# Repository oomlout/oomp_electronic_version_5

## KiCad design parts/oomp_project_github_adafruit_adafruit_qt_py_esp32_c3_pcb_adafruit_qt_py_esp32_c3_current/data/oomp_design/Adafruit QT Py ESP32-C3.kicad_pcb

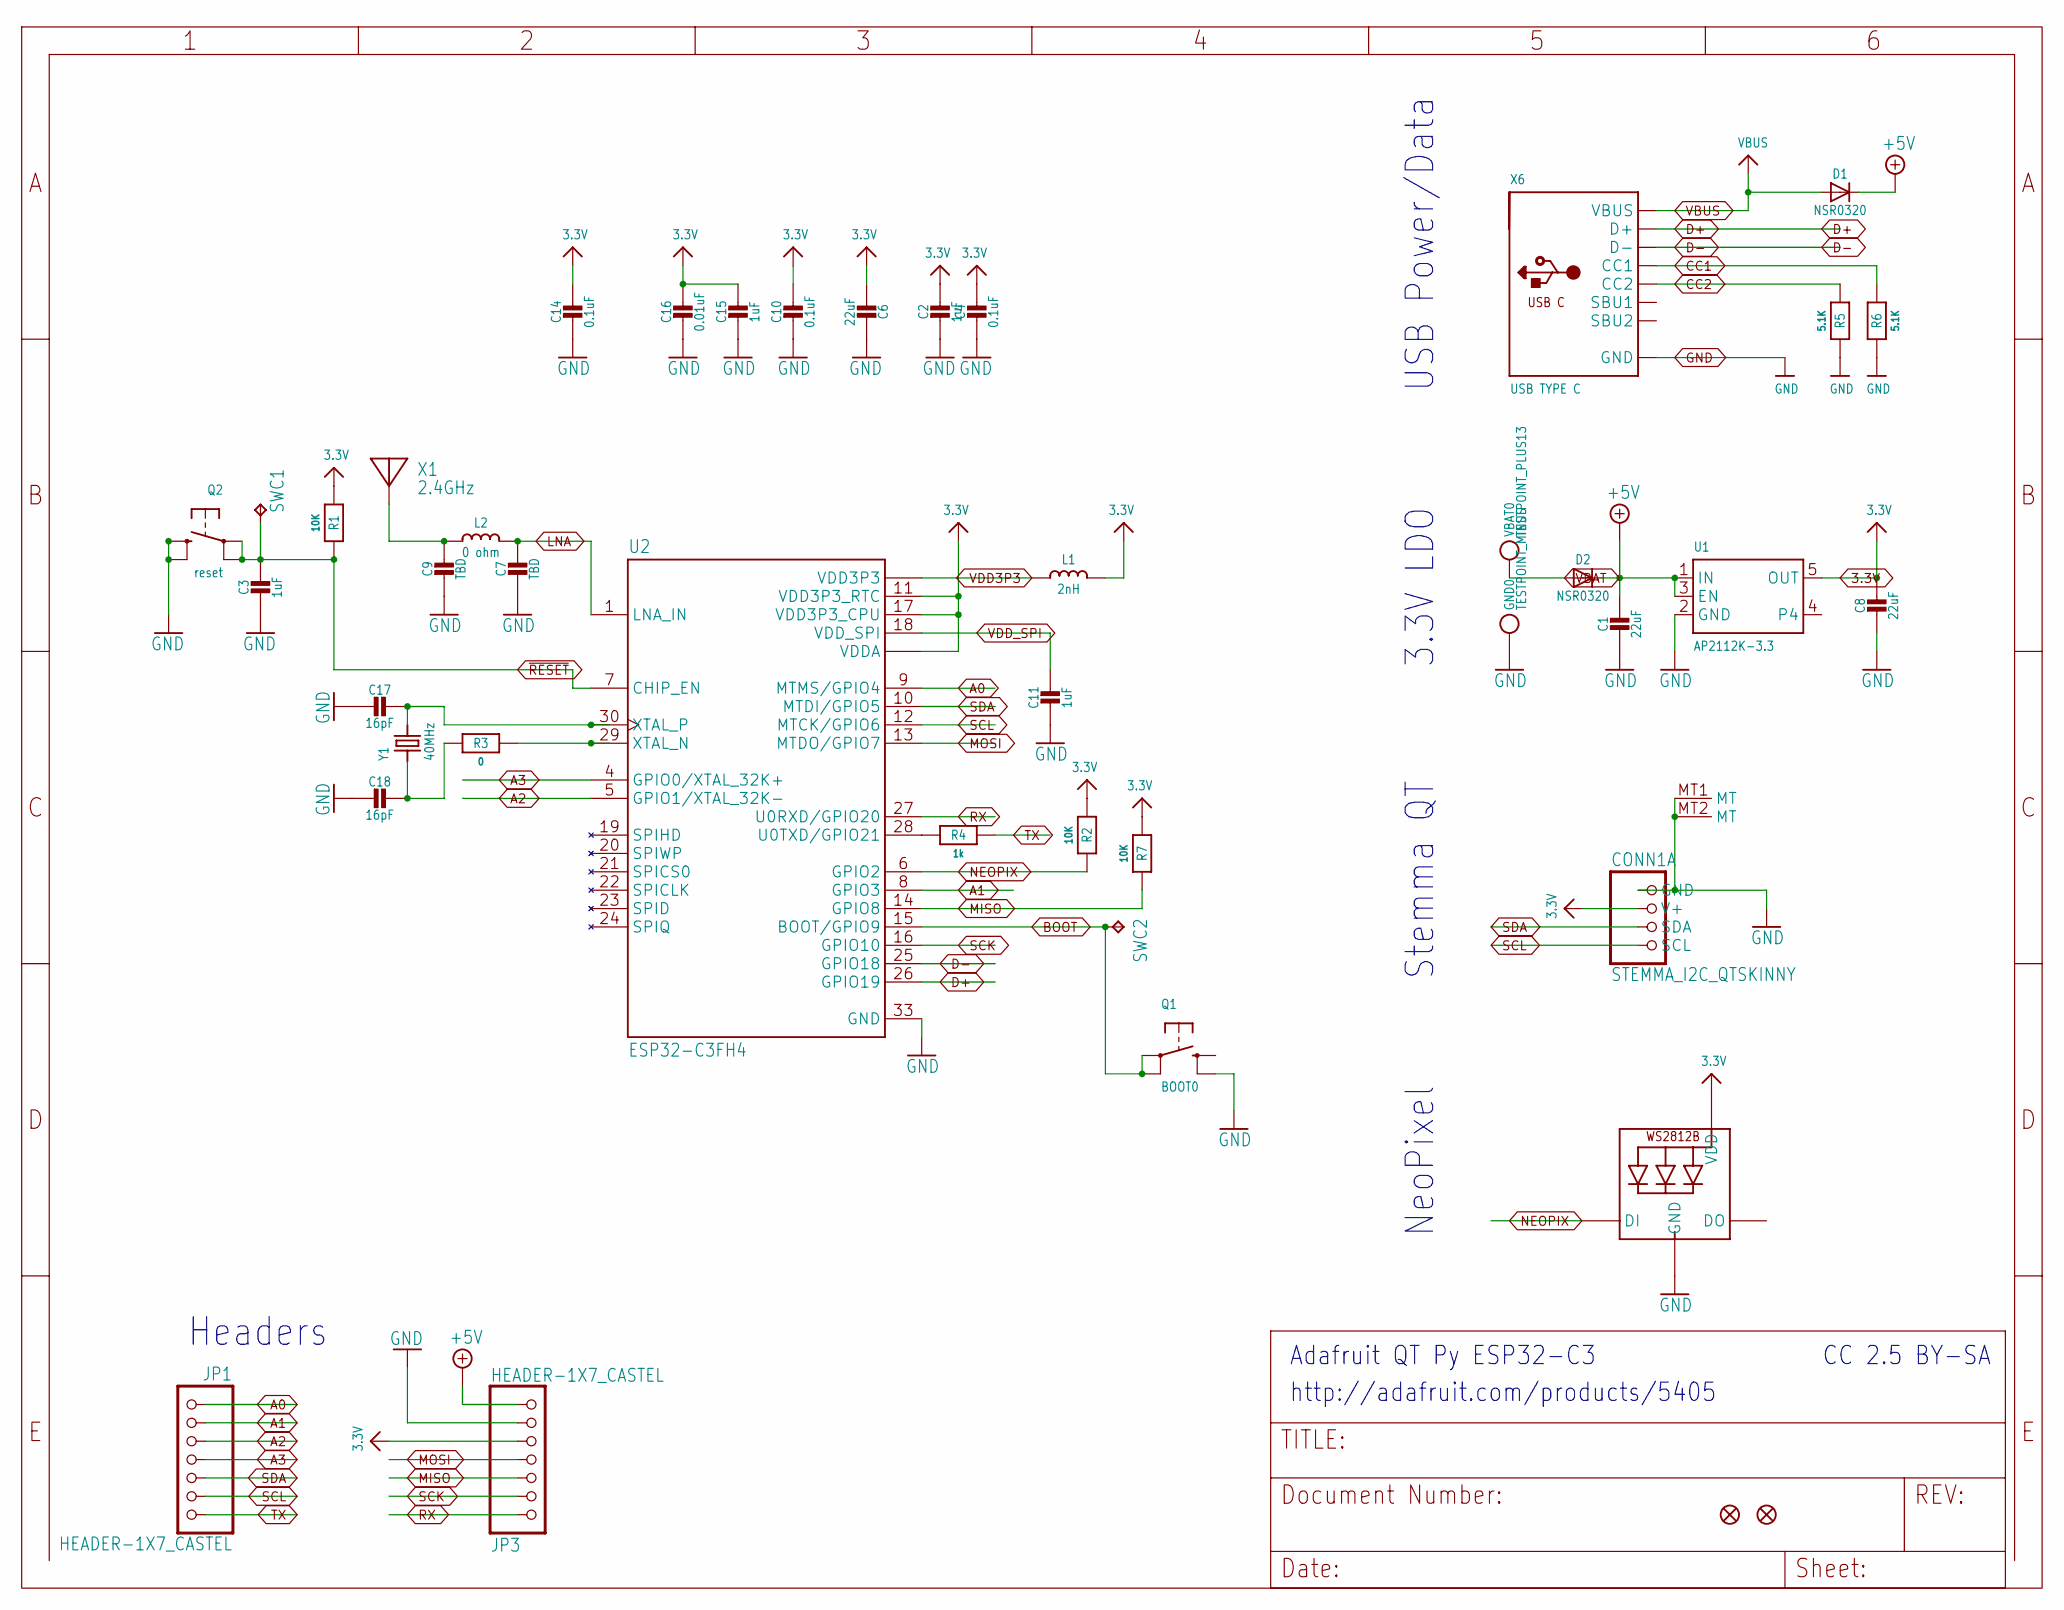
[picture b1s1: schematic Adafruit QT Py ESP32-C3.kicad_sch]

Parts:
C1, C6, C8: 22uF; 0805-NO
C2, C3, C11, C15: 1uF; _0402NO
C4, C10, C14: 0.1uF; _0402NO
C7, C9: TBD; _0402NO
C16: 0.01uF; _0402NO
C17, C18: 16pF; _0402NO
CONN1: STEMMA_I2C_QTSKINNY; JST_SH4_SKINNY
D1, D2: NSR0320; SOD-323_MINI
GND0: TESTPOINT_MINUS; TESTPOINT_MINUS_1X3MM
JP1, JP3: HEADER-1X7_CASTEL; 1X07_CASTEL
L1: 2nH; _0402
L2: 0 ohm; _0402
LED1: WS2812B_SK6805_1515; SK6805_1515
Q1: BOOT0; BTN_KMR2_4.6X2.8
Q2: reset; BTN_KMR2_SLIM
R1, R2: 10K; _0402NO
R3: 0; _0402NO
R4: 1k; _0402NO
R5, R6: 5.1K; _0402NO
R7: 10K; _0603MP_TWO6MIL
SWC1, SWC2: TPB1,27; B1,27
U1: AP2112K-3.3; SOT23-5
U2: ESP32-C3FH4; QFN32_5MM; DIGI-KEY_PART_NUMBER 1904-ESP32-C3FH4CT-ND
U$6, U$8: FIDUCIAL_1MM
VBAT0: TESTPOINT_PLUS13; TESTPOINT_PLUS_1X3MM
X1: 2.4GHz; ANT_2450AT18B100
X6: USB TYPE C; USB_C_CUSB31-CFM2AX-01-X
Y1: 40MHz; CRYSTAL_2X1.6

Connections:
3.3V: C2.1, C4.1, C6.1, C8.1, C10.1, C14.1, C15.1, C16.1, CONN1.2 (V+), JP3.5, JP3.5C (5), L1.1, LED1.2 (VDD), R1.1, R2.1, R7.1, U1.5 (OUT), U2.11 (VDD3P3_RTC), U2.17 (VDD3P3_CPU), U2.31 (VDDA), U2.32 (VDDA)
+5V: C1.1, D1.C, D2.C, JP3.7, JP3.7C (7), U1.1 (IN), U1.3 (EN)
A0: JP1.1, JP1.1C (1), U2.9 (MTMS/GPIO4)
A1: JP1.2, JP1.2C (2), U2.8 (GPIO3)
A2: JP1.3, JP1.3C (3), U2.5 (GPIO1/XTAL_32K-)
A3: JP1.4, JP1.4C (4), U2.4 (GPIO0/XTAL_32K+)
BOOT: Q1.A, Q1.A' (P1), SWC2.TP, U2.15 (BOOT/GPIO9)
CC1: R6.2, X6.A5 (CC1)
CC2: R5.2, X6.B5 (CC2)
D+: U2.26 (GPIO19), X6.A6 (D+), X6.B6 (D+)
D-: U2.25 (GPIO18), X6.A7 (D-), X6.B7 (D-)
GND: C1.2, C2.2, C3.2, C4.2, C6.2, C7.2, C8.2, C9.2, C10.2, C11.2, C14.2, C15.2, C16.2, C17.2, C18.2, CONN1.1 (GND), CONN1.MT1 (MT), CONN1.MT2 (MT), GND0.P$1, JP3.6, JP3.6C (6), LED1.4 (GND), Q1.B' (S1), Q2.B (S), Q2.B' (S1), R5.1, R6.1, U1.2 (GND), U2.33 (GND), X6.A1B12 (GND), X6.B1A12 (GND)
LNA: C7.1, L2.2, U2.1 (LNA_IN)
MISO: JP3.3, JP3.3C (3), R7.2, U2.14 (GPIO8)
MOSI: JP3.4, JP3.4C (4), U2.13 (MTDO/GPIO7)
unnamed: R4.1, U2.28 (U0TXD/GPIO21)
unnamed: C9.1, L2.1, X1.FP
unnamed: R3.2, U2.29 (XTAL_N)
unnamed: C17.1, U2.30 (XTAL_P), Y1.3 (2)
unnamed: C18.1, R3.1, Y1.1
NEOPIX: LED1.1 (DI), R2.2, U2.6 (GPIO2)
RX: JP3.1, JP3.1C (1), U2.27 (U0RXD/GPIO20)
SCK: JP3.2, JP3.2C (2), U2.16 (GPIO10)
SCL: CONN1.4 (SCL), JP1.6, JP1.6C (6), U2.12 (MTCK/GPIO6)
SDA: CONN1.3 (SDA), JP1.5, JP1.5C (5), U2.10 (MTDI/GPIO5)
TX: JP1.7, JP1.7C (7), R4.2
VBAT: D2.A, VBAT0.P$1
VBUS: D1.A, X6.A4B9 (VBUS), X6.B4A9 (VBUS)
VDD3P3: L1.2, U2.2 (VDD3P3), U2.3 (VDD3P3)
VDD_SPI: C11.1, U2.18 (VDD_SPI)
~RESET: C3.1, Q2.A, Q2.A' (P1), R1.2, SWC1.TP, U2.7 (CHIP_EN)

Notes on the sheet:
Adafruit QT Py ESP32-C3
http://adafruit.com/products/5405
CC 2.5 BY-SA
Stemma QT
USB Power/Data
Headers
NeoPixel
3.3V LDO

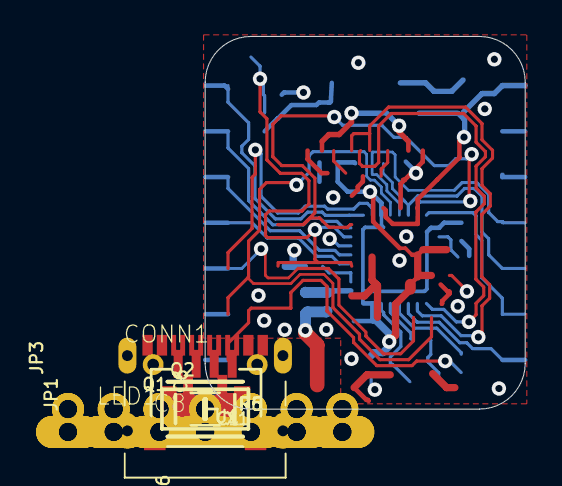
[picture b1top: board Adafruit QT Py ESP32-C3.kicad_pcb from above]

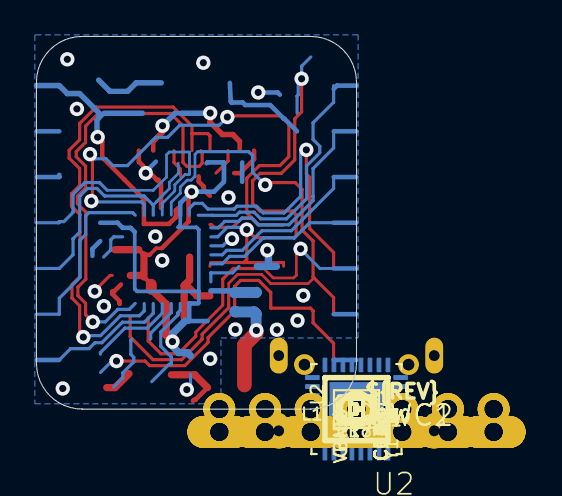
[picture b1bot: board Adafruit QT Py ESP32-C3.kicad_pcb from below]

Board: 4 copper layers, 17.8 x 20.7 mm, 46 parts (29 on the bottom side), 31 nets.

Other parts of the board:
U$3: QTPYC3_TOP
U$12: PCBFEAT-REV-040
U$18: QTPYC3_BOT

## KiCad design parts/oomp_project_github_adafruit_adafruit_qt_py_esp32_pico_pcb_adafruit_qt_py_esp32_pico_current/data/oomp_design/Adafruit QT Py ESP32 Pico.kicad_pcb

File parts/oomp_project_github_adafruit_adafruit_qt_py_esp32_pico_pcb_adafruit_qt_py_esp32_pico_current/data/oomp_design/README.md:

# OOMP KiCad design copy

Open `Adafruit QT Py ESP32 Pico.kicad_pro` (or the `.kicad_pcb` / `.kicad_sch`) in KiCad. Local OOMP libraries are under `libraries/`. Original inputs are preserved in [../original/](../original/).

Only verified unchanged installed KiCad defaults were renamed. Modified, custom, unmatched and unavailable items remain unchanged. Soldering variants are never swapped during conversion. Existing pad coordinates, nets and UUIDs are preserved.

See [conversion_report.yaml](conversion_report.yaml) for every conversion and skip. Copy this directory before editing; regeneration refuses to overwrite edited design files.

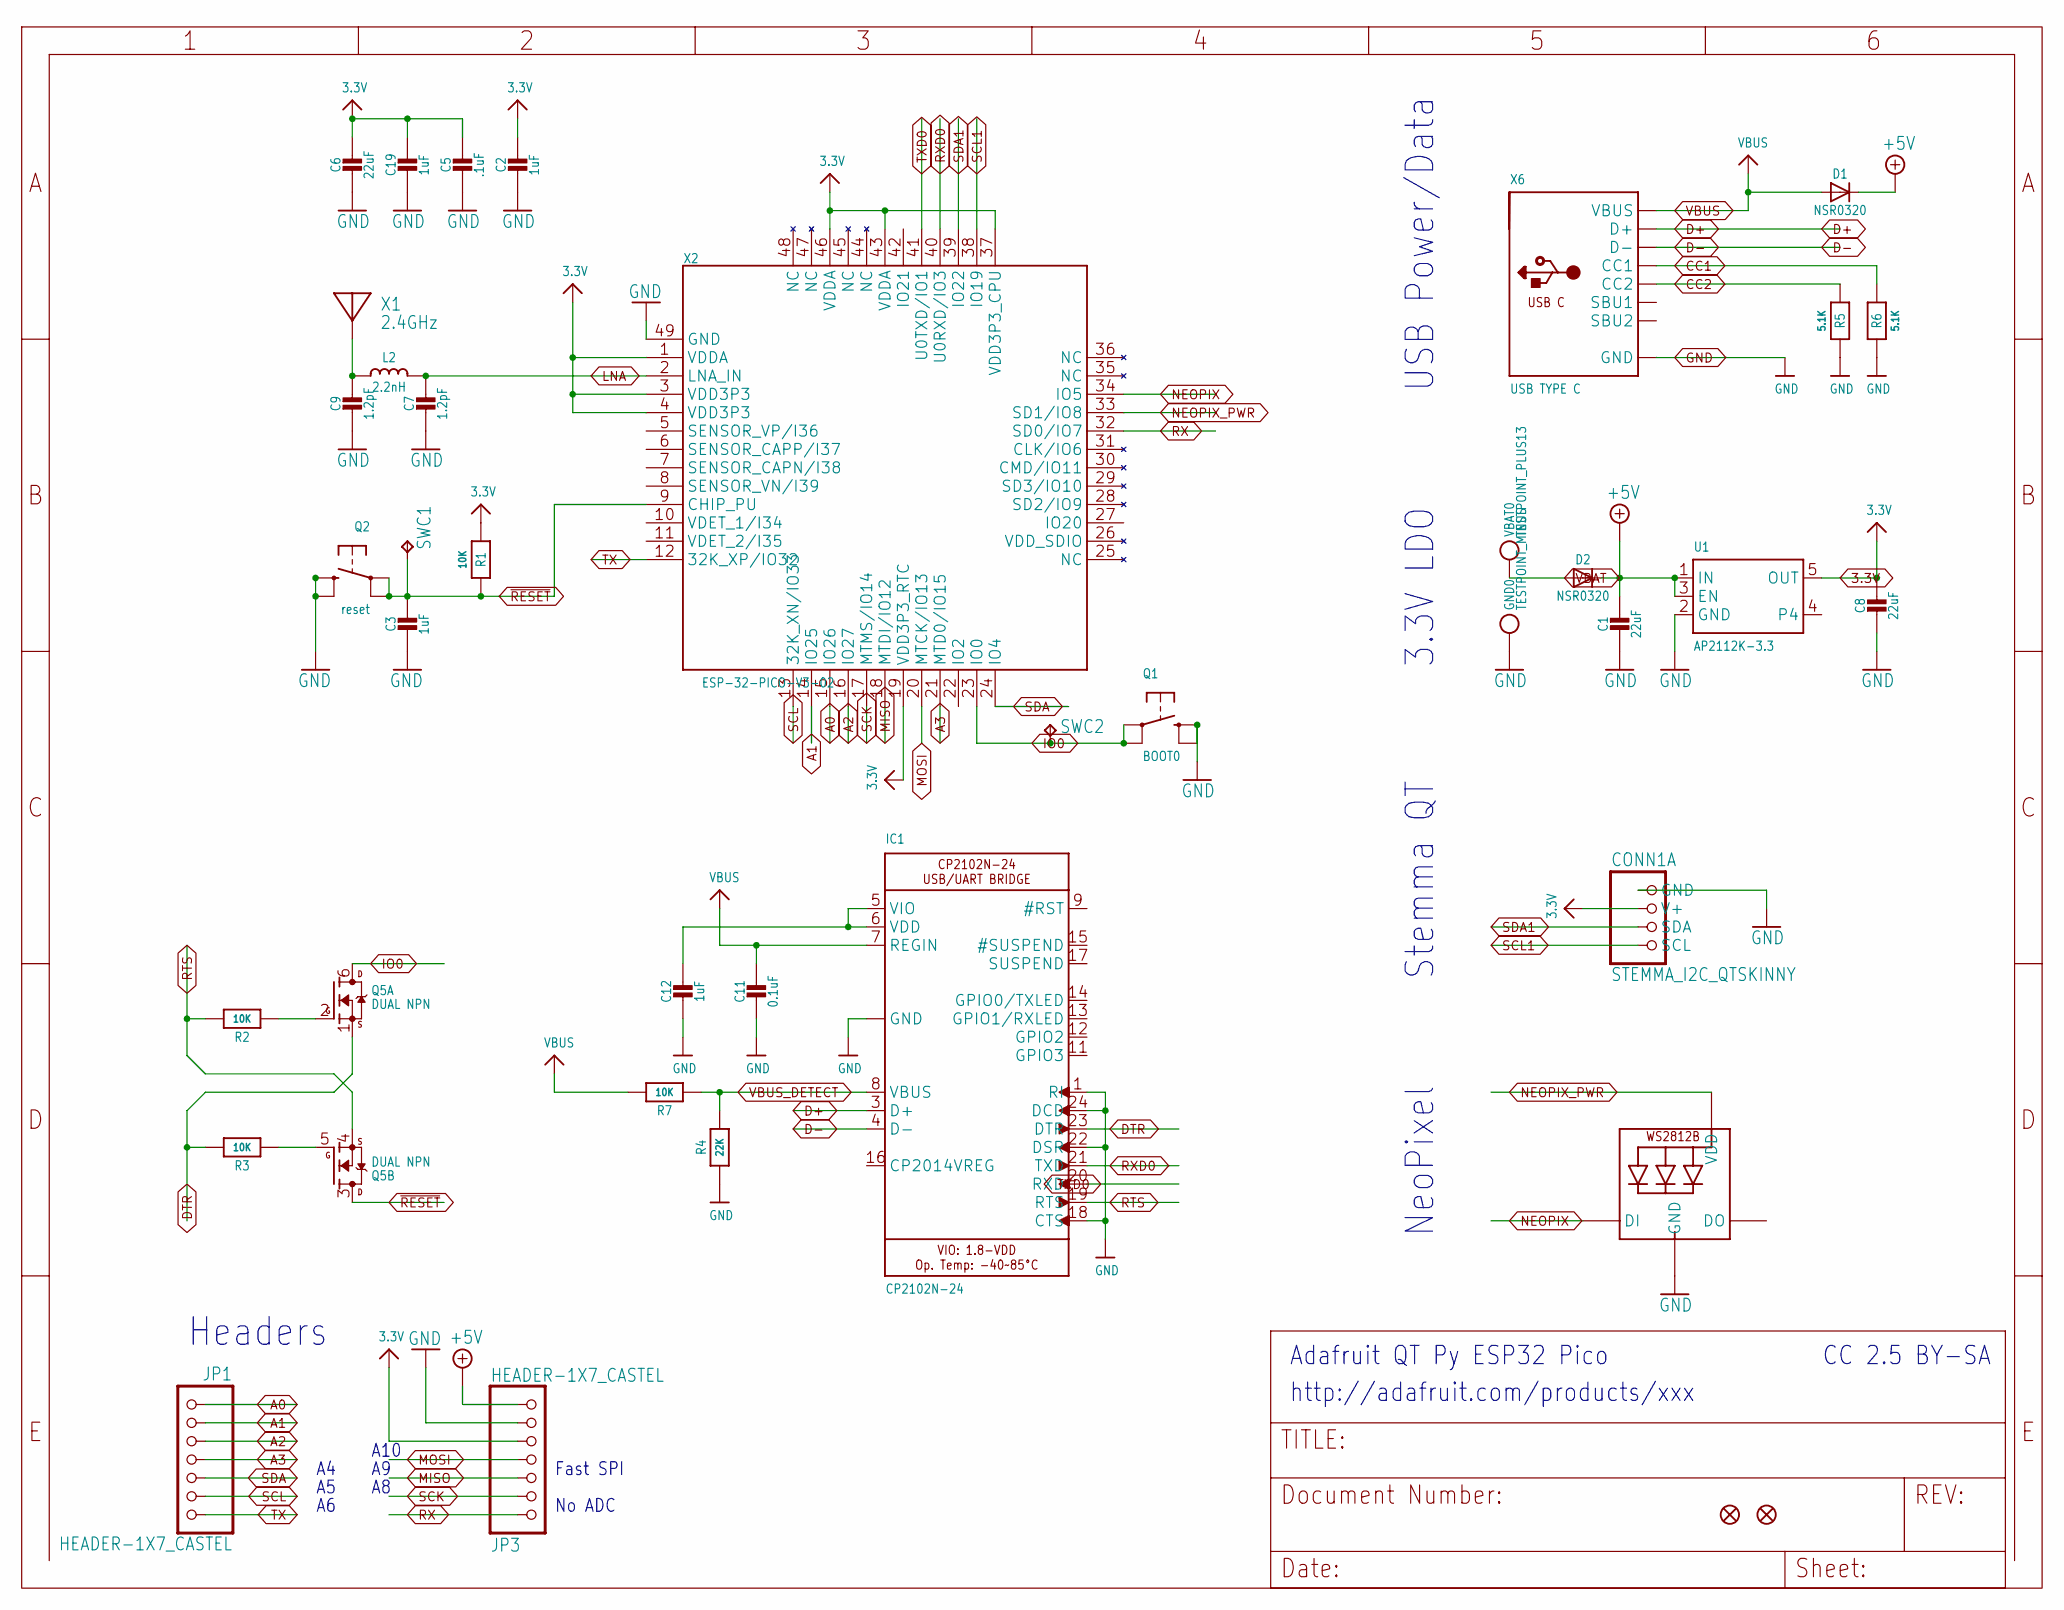
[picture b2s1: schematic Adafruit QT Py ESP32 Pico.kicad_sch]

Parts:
C1, C6, C8: 22uF; 0805-NO
C2, C3, C12: 1uF; _0402NO
C5: .1uF; _0402NO
C7, C9: 1.2pF; _0402NO
C11: 0.1uF; _0402NO
C19: 1uF; 0603-NO_WIDE
CONN1: STEMMA_I2C_QTSKINNY; JST_SH4_SKINNY
D1, D2: NSR0320; SOD-323_MINI
GND0: TESTPOINT_MINUS; TESTPOINT_MINUS_1X3MM
IC1: CP2102N-24; QFN24_4MM_SMSC
JP1, JP3: HEADER-1X7_CASTEL; 1X07_CASTEL
L2: 2.2nH; _0402
LED1: WS2812B_SK6805_1515; SK6805_1515
Q1: BOOT0; BTN_KMR2_4.6X2.8
Q2: reset; BTN_KMR2_4.6X2.8
Q5: DUAL NPN; SOT363
R1, R2, R3, R7: 10K; _0402NO
R4: 22K; _0402NO
R5, R6: 5.1K; _0402NO
SWC1, SWC2: TPB1,27; B1,27
U1: AP2112K-3.3; SOT23-5
U$6, U$8: FIDUCIAL_1MM
VBAT0: TESTPOINT_PLUS13; TESTPOINT_PLUS_1X3MM
X1: 2.4GHz; ANT_2450AT18B100
X2: ESP-32-PICO-V3-02; QFN48_7X7
X6: USB TYPE C; USB_C_CUSB31-CFM2AX-01-X

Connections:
3.3V: C2.1, C5.1, C6.1, C8.1, C19.1, CONN1.2 (V+), JP3.5, JP3.5C (5), R1.1, U1.5 (OUT), X2.1 (VDDA), X2.3 (VDD3P3), X2.4 (VDD3P3), X2.19 (VDD3P3_RTC), X2.37 (VDD3P3_CPU), X2.43 (VDDA), X2.46 (VDDA)
+5V: C1.1, D1.C, D2.C, JP3.7, JP3.7C (7), U1.1 (IN), U1.3 (EN)
A0: JP1.1, JP1.1C (1), X2.15 (IO26)
A1: JP1.2, JP1.2C (2), X2.14 (IO25)
A2: JP1.3, JP1.3C (3), X2.16 (IO27)
A3: JP1.4, JP1.4C (4), X2.21 (MTD0/IO15)
CC1: R6.2, X6.A5 (CC1)
CC2: R5.2, X6.B5 (CC2)
D+: IC1.3 (D+), X6.A6 (D+), X6.B6 (D+)
D-: IC1.4 (D-), X6.A7 (D-), X6.B7 (D-)
DTR: IC1.23 (DTR), Q5.1 (S), R3.2
GND: C1.2, C2.2, C3.2, C5.2, C6.2, C7.2, C8.2, C9.2, C11.2, C12.2, C19.2, CONN1.1 (GND), GND0.P$1, IC1.1 (RI), IC1.2 (GND), IC1.18 (CTS), IC1.22 (DSR), IC1.24 (DCD), IC1.THERM (GND), JP3.6, JP3.6C (6), LED1.4 (GND), Q1.B (S), Q1.B' (S1), Q2.B (S), Q2.B' (S1), R4.1, R5.1, R6.1, U1.2 (GND), X2.49 (GND), X6.A1B12 (GND), X6.B1A12 (GND)
IO0: Q1.A, Q1.A' (P1), Q5.6 (D), SWC2.TP, X2.23 (IO0)
LNA: C7.1, L2.2, X2.2 (LNA_IN)
MISO: JP3.3, JP3.3C (3), X2.18 (MTDI/IO12)
MOSI: JP3.4, JP3.4C (4), X2.20 (MTCK/IO13)
unnamed: C12.1, IC1.5 (VIO), IC1.6 (VDD)
unnamed: C9.1, L2.1, X1.FP
unnamed: Q5.5 (G), R3.1
unnamed: Q5.2 (G), R2.1
NEOPIX: LED1.1 (DI), X2.34 (IO5)
NEOPIX_PWR: LED1.2 (VDD), X2.33 (SD1/IO8)
RTS: IC1.19 (RTS), Q5.4 (S), R2.2
RX: JP3.1, JP3.1C (1), X2.32 (SD0/IO7)
RXD0: IC1.21 (TXD), X2.40 (U0RXD/IO3)
SCK: JP3.2, JP3.2C (2), X2.17 (MTMS/IO14)
SCL: JP1.6, JP1.6C (6), X2.13 (32K_XN/IO33)
SCL1: CONN1.4 (SCL), X2.38 (IO19)
SDA: JP1.5, JP1.5C (5), X2.24 (IO4)
SDA1: CONN1.3 (SDA), X2.39 (IO22)
TX: JP1.7, JP1.7C (7), X2.12 (32K_XP/IO32)
TXD0: IC1.20 (RXD), X2.41 (U0TXD/IO1)
VBAT: D2.A, VBAT0.P$1
VBUS: C11.1, D1.A, IC1.7 (REGIN), R7.2, X6.A4B9 (VBUS), X6.B4A9 (VBUS)
VBUS_DETECT: IC1.8 (VBUS), R4.2, R7.1
~RESET: C3.1, Q2.A, Q2.A' (P1), Q5.3 (D), R1.2, SWC1.TP, X2.9 (CHIP_PU)

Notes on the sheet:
http://adafruit.com/products/xxx
Fast SPI
3.3V LDO
CC 2.5 BY-SA
NeoPixel
Stemma QT
A10
Adafruit QT Py ESP32 Pico
Headers
No ADC
USB Power/Data

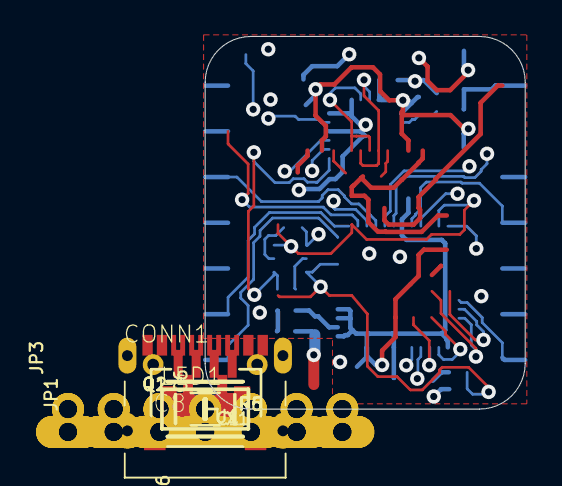
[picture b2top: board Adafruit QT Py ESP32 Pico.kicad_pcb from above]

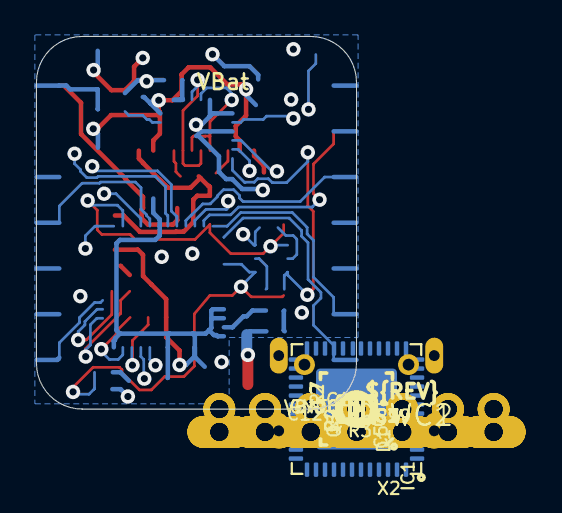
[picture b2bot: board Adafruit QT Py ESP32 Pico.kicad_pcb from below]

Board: 4 copper layers, 17.8 x 20.7 mm, 42 parts (25 on the bottom side), 36 nets.

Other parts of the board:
U$3: QTPY_ESP32_BOT
U$12: PCBFEAT-REV-040
U$22: QTPY_ESP32_TOP

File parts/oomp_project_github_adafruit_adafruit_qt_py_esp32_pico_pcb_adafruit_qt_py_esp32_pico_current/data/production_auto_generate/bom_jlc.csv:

Comment,Designator,Footprint,LCSC Part #
,"JP1,JP3",Adafruit QT Py ESP32 Pico-import-fps:1X07_CASTEL,C7501585
,U$12,Adafruit QT Py ESP32 Pico-import-fps:PCBFEAT-REV-040,
,U$3,Adafruit QT Py ESP32 Pico-import-fps:QTPY_ESP32_BOT,
,U$22,Adafruit QT Py ESP32 Pico-import-fps:QTPY_ESP32_TOP,
,GND0,Adafruit QT Py ESP32 Pico-import-fps:TESTPOINT_MINUS_1X3MM,
,VBAT0,Adafruit QT Py ESP32 Pico-import-fps:TESTPOINT_PLUS_1X3MM,
  NSR0320,"D1,D2",Adafruit QT Py ESP32 Pico-import-fps:SOD-323_MINI,
.1uF,C5,Adafruit QT Py ESP32 Pico-import-fps:_0402NO,
0.1uF,C11,Adafruit QT Py ESP32 Pico-import-fps:_0402NO,C60474
1.2pF,"C7,C9",Adafruit QT Py ESP32 Pico-import-fps:_0402NO,
10K,"R1,R2,R3,R7",Adafruit QT Py ESP32 Pico-import-fps:_0402NO,C2906861
1uF,C19,Adafruit QT Py ESP32 Pico-import-fps:0603-NO_WIDE,C5673
1uF,"C2,C3,C12",Adafruit QT Py ESP32 Pico-import-fps:_0402NO,C2887021
2.2nH,L2,Adafruit QT Py ESP32 Pico-import-fps:_0402,
2.4GHz,X1,Adafruit QT Py ESP32 Pico-import-fps:ANT_2450AT18B100,
22K,R4,Adafruit QT Py ESP32 Pico-import-fps:_0402NO,C82868
22uF,"C1,C6,C8",Adafruit QT Py ESP32 Pico-import-fps:0805-NO,
5.1K,"R5,R6",Adafruit QT Py ESP32 Pico-import-fps:_0402NO,C25905
AP2112K-3.3,U1,Adafruit QT Py ESP32 Pico-import-fps:SOT23-5,
BOOT0,Q1,Adafruit QT Py ESP32 Pico-import-fps:BTN_KMR2_4.6X2.8,
CP2102N-24,IC1,Adafruit QT Py ESP32 Pico-import-fps:QFN24_4MM_SMSC,
DUAL NPN,Q5,Adafruit QT Py ESP32 Pico-import-fps:SOT363,
ESP-32-PICO-V3-02,X2,Adafruit QT Py ESP32 Pico-import-fps:QFN48_7X7,
FIDUCIAL_1MM,"U$6,U$8",Adafruit QT Py ESP32 Pico-import-fps:FIDUCIAL_1MM,
reset,Q2,Adafruit QT Py ESP32 Pico-import-fps:BTN_KMR2_4.6X2.8,
STEMMA_I2C_QTSKINNY,CONN1,Adafruit QT Py ESP32 Pico-import-fps:JST_SH4_SKINNY,
"TPB1,27","SWC1,SWC2","Adafruit QT Py ESP32 Pico-import-fps:B1,27",
USB TYPE C,X6,Adafruit QT Py ESP32 Pico-import-fps:USB_C_CUSB31-CFM2AX-01-X,
WS2812B_SK6805_1515,LED1,Adafruit QT Py ESP32 Pico-import-fps:SK6805_1515,

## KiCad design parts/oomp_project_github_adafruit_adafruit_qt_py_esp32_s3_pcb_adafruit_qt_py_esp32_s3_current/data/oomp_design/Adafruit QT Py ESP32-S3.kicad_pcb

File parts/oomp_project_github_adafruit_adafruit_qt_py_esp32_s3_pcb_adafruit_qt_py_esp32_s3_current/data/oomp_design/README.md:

# OOMP KiCad design copy

Open `Adafruit QT Py ESP32-S3.kicad_pro` (or the `.kicad_pcb` / `.kicad_sch`) in KiCad. Local OOMP libraries are under `libraries/`. Original inputs are preserved in [../original/](../original/).

Only verified unchanged installed KiCad defaults were renamed. Modified, custom, unmatched and unavailable items remain unchanged. Soldering variants are never swapped during conversion. Existing pad coordinates, nets and UUIDs are preserved.

See [conversion_report.yaml](conversion_report.yaml) for every conversion and skip. Copy this directory before editing; regeneration refuses to overwrite edited design files.

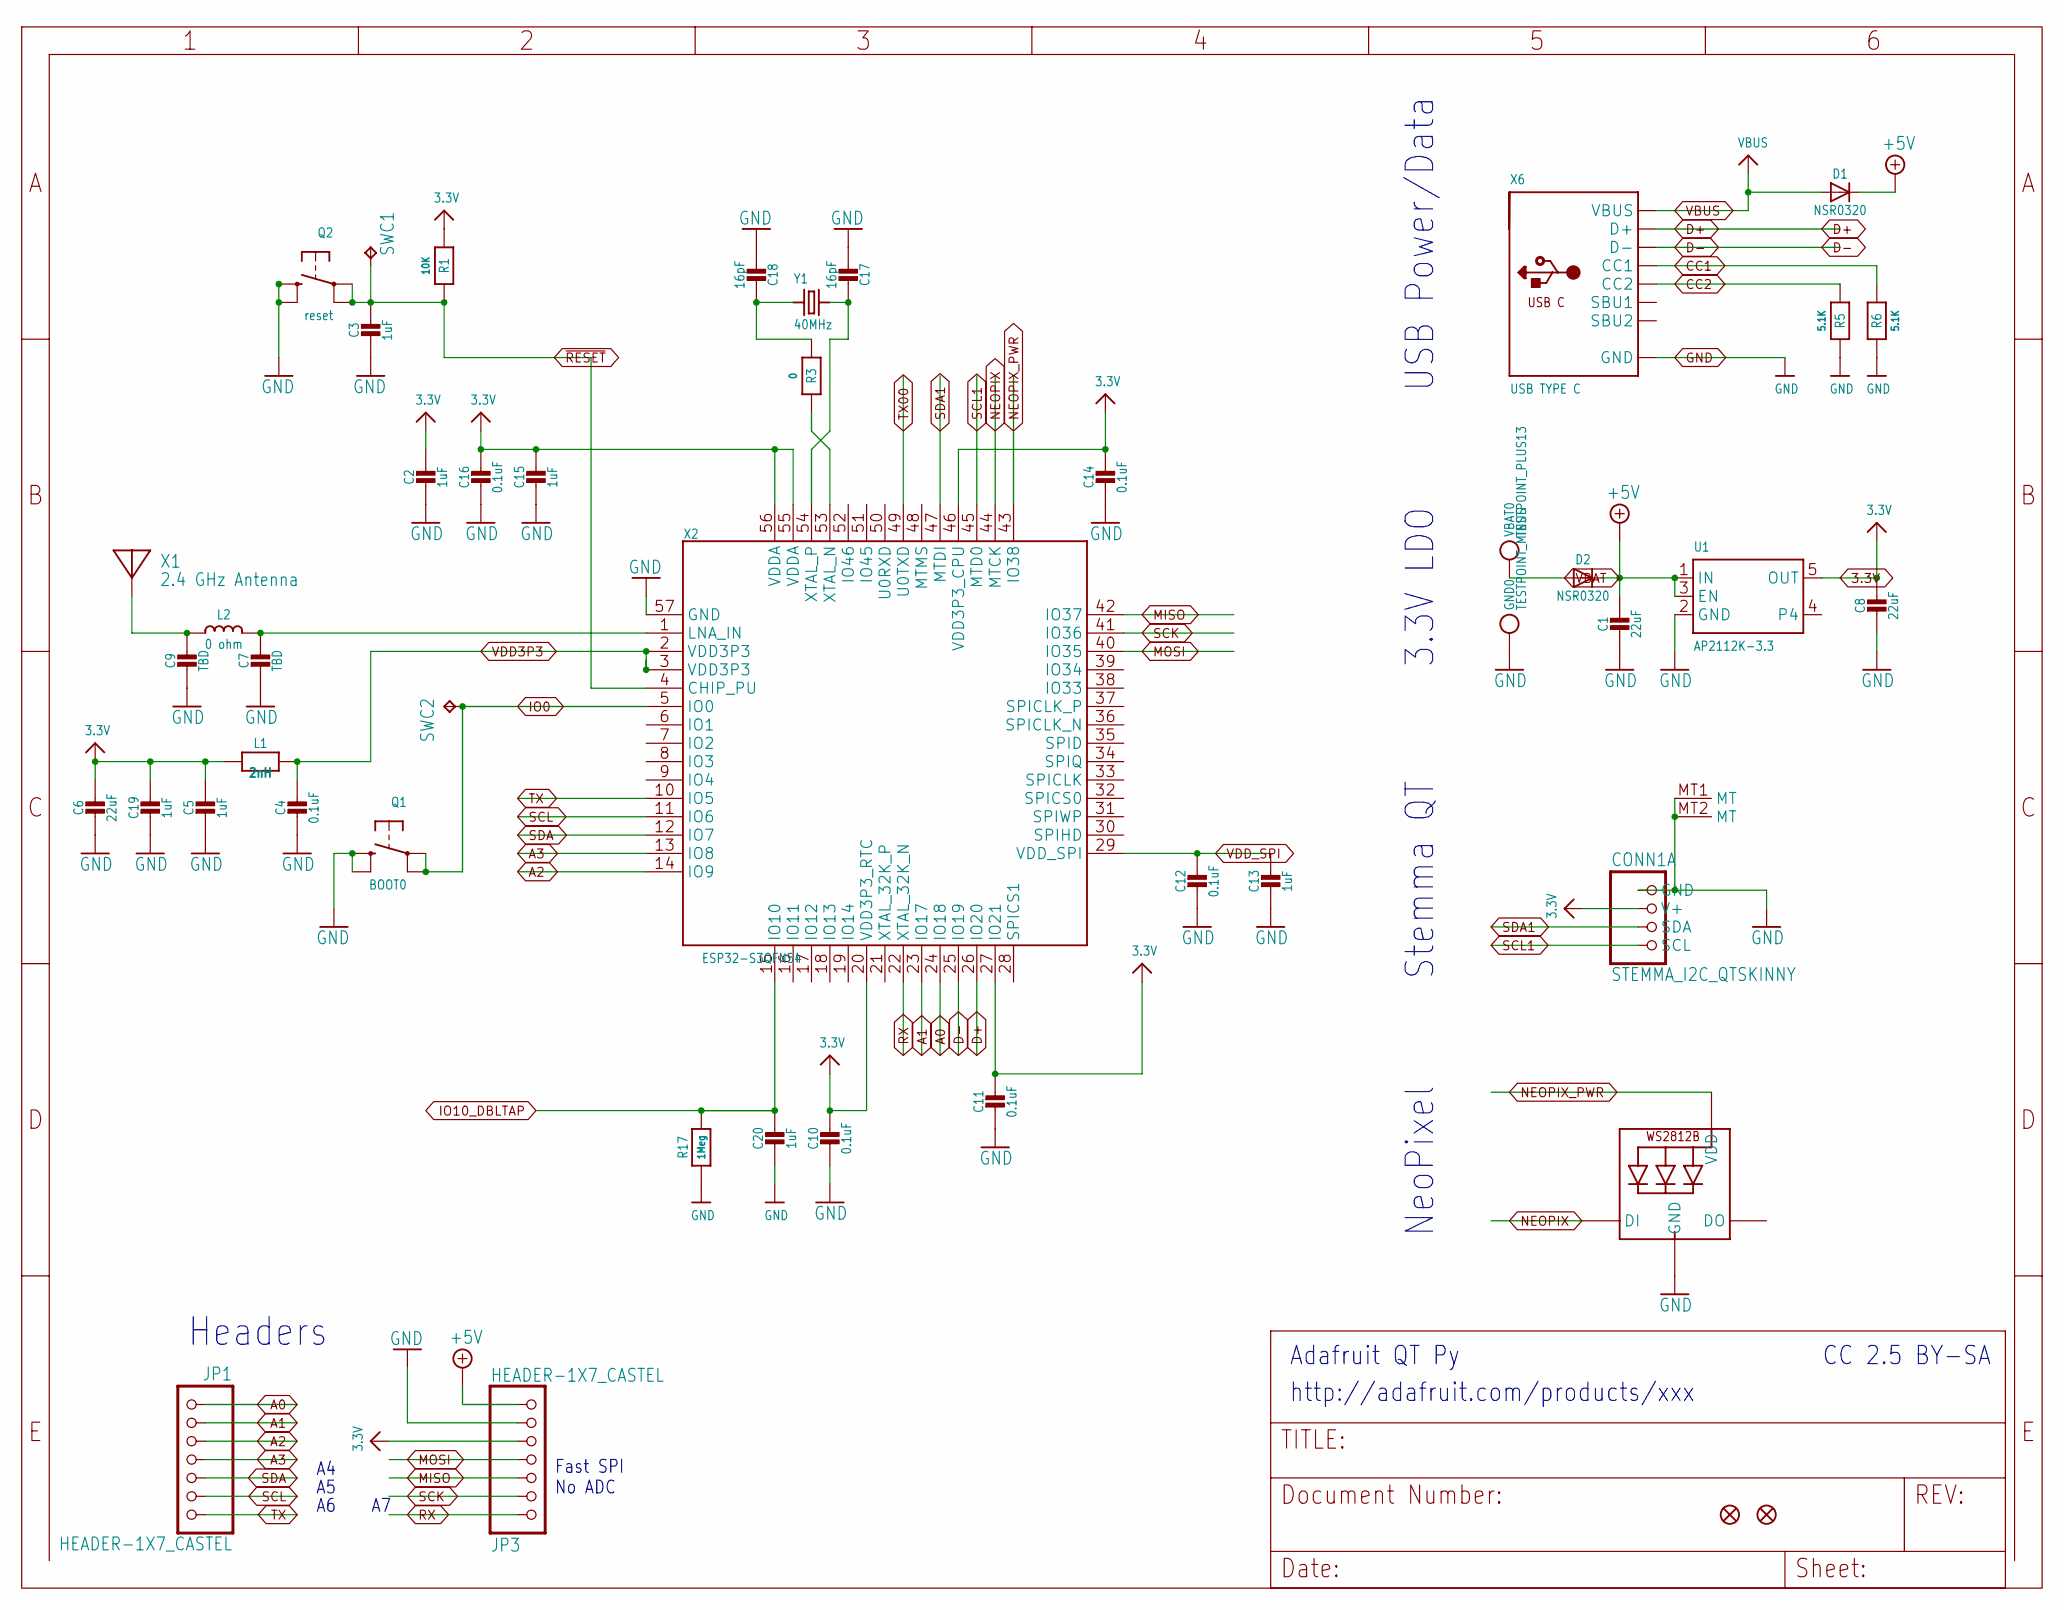
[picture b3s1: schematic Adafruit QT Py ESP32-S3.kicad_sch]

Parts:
C1, C6, C8: 22uF; 0805-NO
C2, C3, C5, C13, C15, C19, C20: 1uF; _0402NO
C4, C10, C11, C12, C14, C16: 0.1uF; _0402NO
C7, C9: TBD; _0402NO
C17, C18: 16pF; _0402NO
CONN1: STEMMA_I2C_QTSKINNY; JST_SH4_SKINNY
D1, D2: NSR0320; SOD-323_MINI
GND0: TESTPOINT_MINUS; TESTPOINT_MINUS_1X3MM
JP1, JP3: HEADER-1X7_CASTEL; 1X07_CASTEL
L1: 2nH; _0402NO
L2: 0 ohm; _0402
LED1: WS2812B_SK6805_1515; SK6805_1515
Q1: BOOT0; BTN_KMR2_4.6X2.8
Q2: reset; BTN_KMR2_4.6X2.8
R1: 10K; _0402NO
R3: 0; _0402NO
R5, R6: 5.1K; _0402NO
R17: 1Meg; _0402NO
SWC1, SWC2: TPB1,27; B1,27
U1: AP2112K-3.3; SOT23-5
U$6, U$8: FIDUCIAL_1MM
VBAT0: TESTPOINT_PLUS13; TESTPOINT_PLUS_1X3MM
X1: 2.4 GHz Antenna; ANT_2450AT18B100
X2: ESP32-S3QFN54; QFN56_7X7; DIGI-KEY_PART_NUMBER 1965-ESP32-S2CT-ND
X6: USB TYPE C; USB_C_CUSB31-CFM2AX-01-X
Y1: 40MHz; CRYSTAL_2X1.6

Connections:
3.3V: C2.1, C5.1, C6.1, C8.1, C10.1, C11.1, C14.1, C15.1, C16.1, C19.1, CONN1.2 (V+), JP3.5, JP3.5C (5), L1.1, R1.1, U1.5 (OUT), X2.20 (VDD3P3_RTC), X2.27 (IO21), X2.46 (VDD3P3_CPU), X2.55 (VDDA), X2.56 (VDDA)
+5V: C1.1, D1.C, D2.C, JP3.7, JP3.7C (7), U1.1 (IN), U1.3 (EN)
A0: JP1.1, JP1.1C (1), X2.24 (IO18)
A1: JP1.2, JP1.2C (2), X2.23 (IO17)
A2: JP1.3, JP1.3C (3), X2.14 (IO9)
A3: JP1.4, JP1.4C (4), X2.13 (IO8)
CC1: R6.2, X6.A5 (CC1)
CC2: R5.2, X6.B5 (CC2)
D+: X2.26 (IO20), X6.A6 (D+), X6.B6 (D+)
D-: X2.25 (IO19), X6.A7 (D-), X6.B7 (D-)
GND: C1.2, C2.2, C3.2, C4.2, C5.2, C6.2, C7.2, C8.2, C9.2, C10.2, C11.2, C12.2, C13.2, C14.2, C15.2, C16.2, C17.2, C18.2, C19.2, C20.2, CONN1.1 (GND), CONN1.MT1 (MT), CONN1.MT2 (MT), GND0.P$1, JP3.6, JP3.6C (6), LED1.4 (GND), Q1.B (S), Q1.B' (S1), Q2.B (S), Q2.B' (S1), R5.1, R6.1, R17.1, U1.2 (GND), X2.57 (GND), X6.A1B12 (GND), X6.B1A12 (GND)
IO0: Q1.A, Q1.A' (P1), SWC2.TP, X2.5 (IO0)
IO10_DBLTAP: C20.1, R17.2, X2.15 (IO10)
MISO: JP3.3, JP3.3C (3), X2.42 (IO37)
MOSI: JP3.4, JP3.4C (4), X2.40 (IO35)
unnamed: R3.2, X2.53 (XTAL_N)
unnamed: C7.1, L2.2, X2.1 (LNA_IN)
unnamed: C9.1, L2.1, X1.FP
unnamed: C17.1, X2.54 (XTAL_P), Y1.3 (2)
unnamed: C18.1, R3.1, Y1.1
NEOPIX: LED1.1 (DI), X2.44 (MTCK)
NEOPIX_PWR: LED1.2 (VDD), X2.43 (IO38)
RX: JP3.1, JP3.1C (1), X2.22 (XTAL_32K_N)
SCK: JP3.2, JP3.2C (2), X2.41 (IO36)
SCL: JP1.6, JP1.6C (6), X2.11 (IO6)
SCL1: CONN1.4 (SCL), X2.45 (MTD0)
SDA: JP1.5, JP1.5C (5), X2.12 (IO7)
SDA1: CONN1.3 (SDA), X2.47 (MTDI)
TX: JP1.7, JP1.7C (7), X2.10 (IO5)
TX00: X2.49 (U0TXD)
VBAT: D2.A, VBAT0.P$1
VBUS: D1.A, X6.A4B9 (VBUS), X6.B4A9 (VBUS)
VDD3P3: C4.1, L1.2, X2.2 (VDD3P3), X2.3 (VDD3P3)
VDD_SPI: C12.1, C13.1, X2.29 (VDD_SPI)
~RESET: C3.1, Q2.A, Q2.A' (P1), R1.2, SWC1.TP, X2.4 (CHIP_PU)

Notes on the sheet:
Stemma QT
CC 2.5 BY-SA
USB Power/Data
http://adafruit.com/products/xxx
Headers
Adafruit QT Py
NeoPixel
Fast SPI No ADC
3.3V LDO

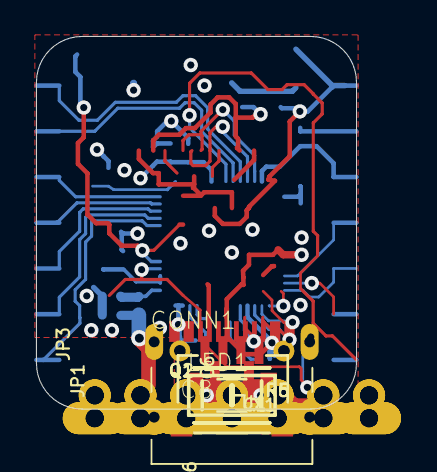
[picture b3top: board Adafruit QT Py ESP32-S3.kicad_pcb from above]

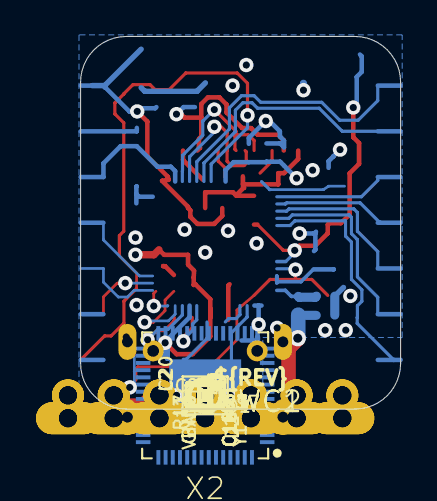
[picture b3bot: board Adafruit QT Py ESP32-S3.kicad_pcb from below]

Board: 4 copper layers, 17.8 x 20.7 mm, 49 parts (32 on the bottom side), 34 nets.

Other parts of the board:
U$7: QTPY_ESP32_TOP
U$11: QTPYS3_BOT
U$12: PCBFEAT-REV-040

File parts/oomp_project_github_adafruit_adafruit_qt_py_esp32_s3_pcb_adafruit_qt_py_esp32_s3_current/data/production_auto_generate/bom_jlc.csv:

Comment,Designator,Footprint,LCSC Part #
,"JP1,JP3",Adafruit QT Py ESP32-S3-import-fps:1X07_CASTEL,C7501585
,U$12,Adafruit QT Py ESP32-S3-import-fps:PCBFEAT-REV-040,
,U$7,Adafruit QT Py ESP32-S3-import-fps:QTPY_ESP32_TOP,
,U$11,Adafruit QT Py ESP32-S3-import-fps:QTPYS3_BOT,
,GND0,Adafruit QT Py ESP32-S3-import-fps:TESTPOINT_MINUS_1X3MM,
,VBAT0,Adafruit QT Py ESP32-S3-import-fps:TESTPOINT_PLUS_1X3MM,
  NSR0320,"D1,D2",Adafruit QT Py ESP32-S3-import-fps:SOD-323_MINI,
0,R3,Adafruit QT Py ESP32-S3-import-fps:_0402NO,C2906877
0 ohm,L2,Adafruit QT Py ESP32-S3-import-fps:_0402,
0.1uF,"C4,C10,C11,C12,C14,C16",Adafruit QT Py ESP32-S3-import-fps:_0402NO,C60474
10K,R1,Adafruit QT Py ESP32-S3-import-fps:_0402NO,C2906861
16pF,"C17,C18",Adafruit QT Py ESP32-S3-import-fps:_0402NO,
1Meg,R17,Adafruit QT Py ESP32-S3-import-fps:_0402NO,C2906900
1uF,"C2,C3,C5,C13,C15,C19,C20",Adafruit QT Py ESP32-S3-import-fps:_0402NO,C2887021
2.4 GHz Antenna,X1,Adafruit QT Py ESP32-S3-import-fps:ANT_2450AT18B100,
22uF,"C1,C6,C8",Adafruit QT Py ESP32-S3-import-fps:0805-NO,
2nH,L1,Adafruit QT Py ESP32-S3-import-fps:_0402NO,
40MHz,Y1,Adafruit QT Py ESP32-S3-import-fps:CRYSTAL_2X1.6,
5.1K,"R5,R6",Adafruit QT Py ESP32-S3-import-fps:_0402NO,C25905
AP2112K-3.3,U1,Adafruit QT Py ESP32-S3-import-fps:SOT23-5,
BOOT0,Q1,Adafruit QT Py ESP32-S3-import-fps:BTN_KMR2_4.6X2.8,
ESP32-S3QFN54,X2,Adafruit QT Py ESP32-S3-import-fps:QFN56_7X7,
FIDUCIAL_1MM,"U$6,U$8",Adafruit QT Py ESP32-S3-import-fps:FIDUCIAL_1MM,
reset,Q2,Adafruit QT Py ESP32-S3-import-fps:BTN_KMR2_4.6X2.8,
STEMMA_I2C_QTSKINNY,CONN1,Adafruit QT Py ESP32-S3-import-fps:JST_SH4_SKINNY,
TBD,"C7,C9",Adafruit QT Py ESP32-S3-import-fps:_0402NO,
"TPB1,27","SWC1,SWC2","Adafruit QT Py ESP32-S3-import-fps:B1,27",
USB TYPE C,X6,Adafruit QT Py ESP32-S3-import-fps:USB_C_CUSB31-CFM2AX-01-X,
WS2812B_SK6805_1515,LED1,Adafruit QT Py ESP32-S3-import-fps:SK6805_1515,
